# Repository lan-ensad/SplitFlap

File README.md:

# SplitFlap

Project : 

Installation for photographer [exhibition Isabelle Le Minh](https://galeriegaillard.com/exhibitions/206-isabelle-le-minh-postlude/overview/). Design & production by Olivier Bienz and Martin De Bie for six machines.

## list

plans : .dxf et .svg \
`_mod/_exports/_plans`

pcb design : schematic, layout and gerber \
`_pcb/split_falp`

programme : \
two easy code to set motorSpeed and calibrate steps.

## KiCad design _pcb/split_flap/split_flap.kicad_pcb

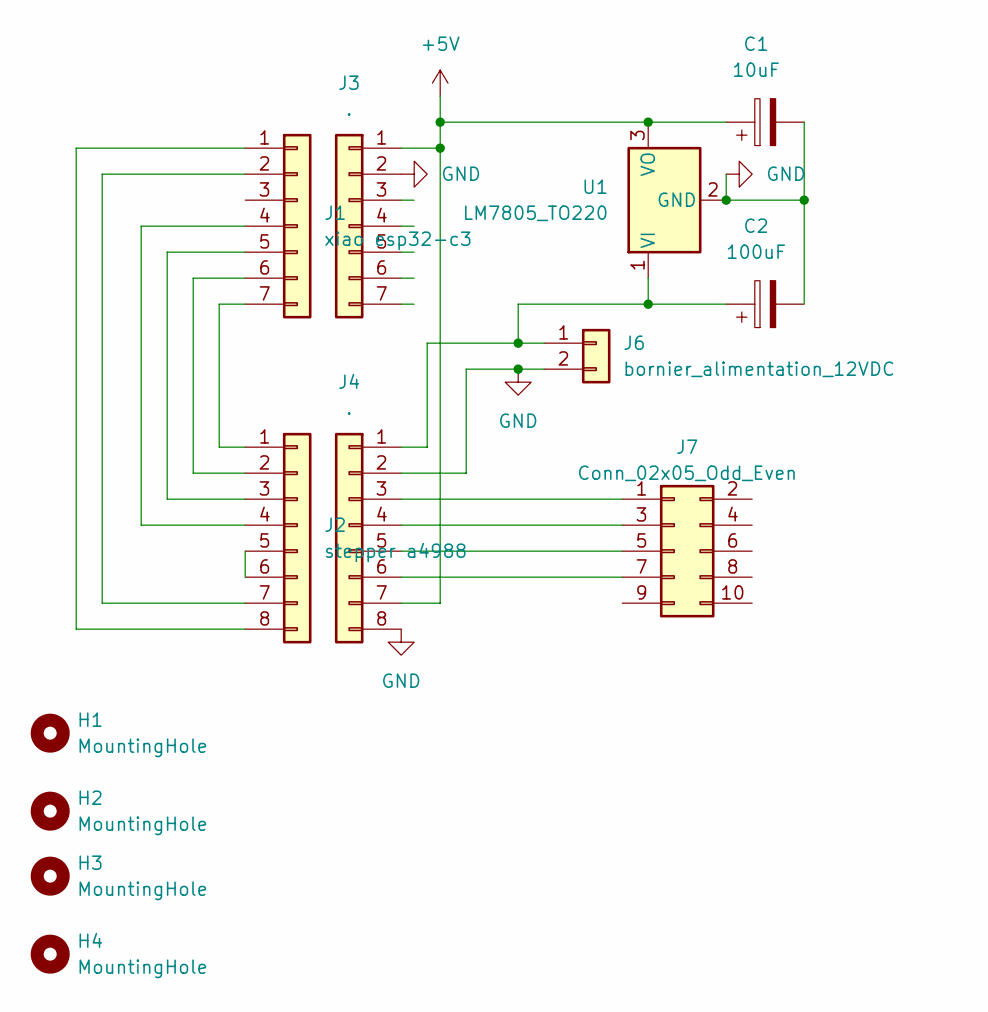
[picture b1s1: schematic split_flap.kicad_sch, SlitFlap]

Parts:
C1: 10uF; CP_Radial_D5.0mm_P2.00mm
C2: 100uF; CP_Radial_D5.0mm_P2.00mm
H1, H2, H3, H4: MountingHole; MountingHole_3.2mm_M3
J1: xiao esp32-c3; PinHeader_1x07_P2.54mm_Vertical
J2: stepper a4988; PinHeader_1x08_P2.54mm_Vertical
J3: .; PinHeader_1x07_P2.54mm_Vertical
J4: .; PinHeader_1x08_P2.54mm_Vertical
J6: bornier_alimentation_12VDC; TerminalBlock_MetzConnect_Type171_RT13702HBWC_1x02_P7.50mm_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
J7: Conn_02x05_Odd_Even; PinHeader_2x05_P2.54mm_Horizontal
U1: LM7805_TO220; TO-220-3_Vertical

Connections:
+5V: C1.1, J3.1, J4.7, U1.3 (VO)
GND: C1.2, C2.2, J3.2, J4.2, J4.8, J6.2, U1.2 (GND)
unnamed: J1.1, J2.8
unnamed: J1.2, J2.7
unnamed: J1.4, J2.4
unnamed: J1.5, J2.3
unnamed: J1.6, J2.2
unnamed: J1.7, J2.1
unnamed: J2.5, J2.6
unnamed: C2.1, J4.1, J6.1, U1.1 (VI)
unnamed: J4.3, J7.1
unnamed: J4.4, J7.3
unnamed: J4.5, J7.5
unnamed: J4.6, J7.7

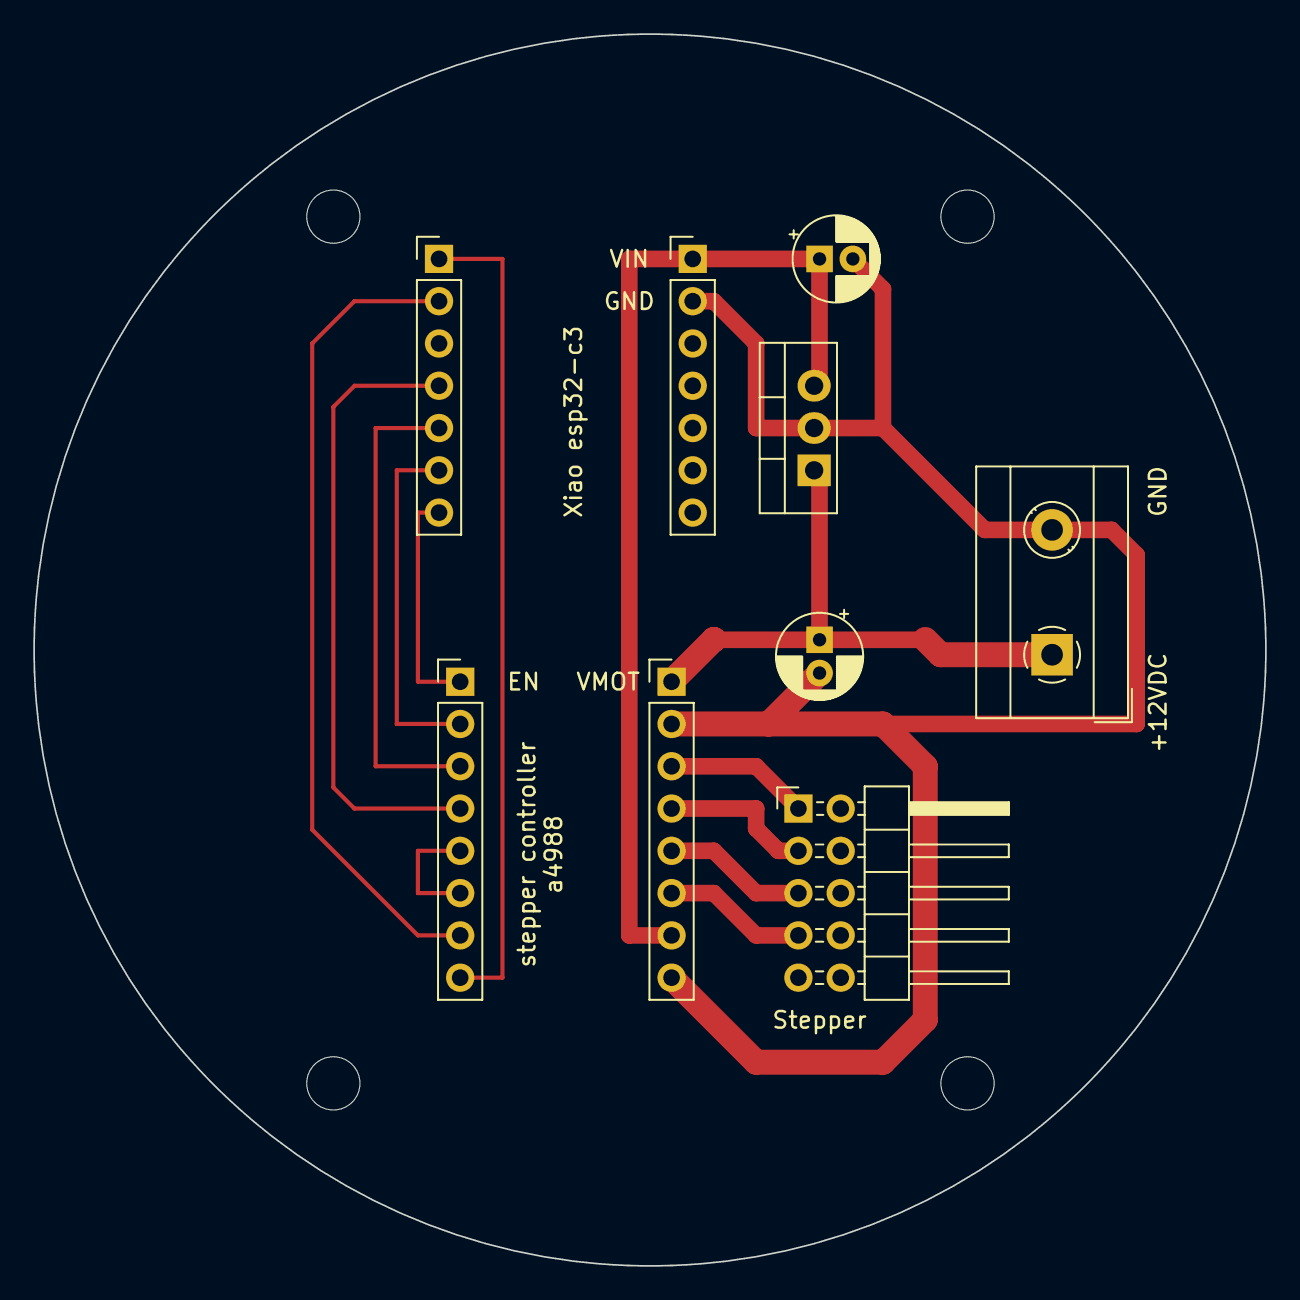
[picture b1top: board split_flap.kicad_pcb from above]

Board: 2 copper layers, 74.0 x 74.0 mm, 13 parts (0 on the bottom side), 14 nets.

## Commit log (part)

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2023-06-16 publish
2023-06-23 create behaviour
2023-06-27 backup
2024-02-10 Create LICENSE
2024-02-10 update publication
2026-02-05 refactor
